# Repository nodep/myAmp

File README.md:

# modulo2

What started as an idea to upgrade the guts of a practice guitar amplifier (Marshall Valvestate 8010), has evolved into a stereo guitar amplifier with effects. The current prototype is housed in a guitar pedal box (119 x 93.5 x 56.5mm). It has a modular design with the preamp, the effects board, and a stereo power amp. These modules are split into their own PCBs.

### The preamp

It is based on ESP's project 27 (https://sound-au.com/project27.htm). I have only used the preamp from this project and I have made a few changes:

- The overdrive section is changed to work as protection and limit the output to 3.3V. This is needed for the inputs of the DSP chip in the effects section (max input of FV-1 is 3.3V).
- The zener diode rail splitter is changed to a TL2426. Reasons being a smaller footprint and much lower power consumption.
- The total gain has been reduced on every stage.
- The tone control values have changed to a more Fender-like sound.

### The effects

The effects sections is based on a Spin semiconductor's FV-1 DSP chip. The chip has 8 built-in effects and the ability to read 8 more effects from an external EEPROM. This was extended using a microcontroller (ATmega328p) to up to 50 external effects which are read from the microcontroller's flash memory. The board also has a dry/wet mixer, a master volume. The microcontroller has a driverless USB bootloader which allows easier firmware updates and DSP program modification. A rotary encoder allows for FV-1 program selection and changing the input clock frequency of the FV-1. Some of the FV-1 programs work as a mono input and produce a stereo output with one channel outputing a slightly different signal to the other creating a stereo effect from a mono preamp input. The microcontroller oversees the power section to avoid audible pops during the power-up and power-down.

### The power amp

The power section is based on a TPA3220 in a stereo configuration. I have not tested it fully yet, but it should be able to output up to 60W into 4Ω per channel. It is a Class-D amp bringing high efficiency (around 90%) and very low distortion and noise. The TPA3220 chip has an integrated preamp with a selectable gain (4 distinct levels) making the full range of the master volume useful for quiter practice and louder performance levels.

The PCBs for the final prototype have been send to the fab.

Stay tuned for results!

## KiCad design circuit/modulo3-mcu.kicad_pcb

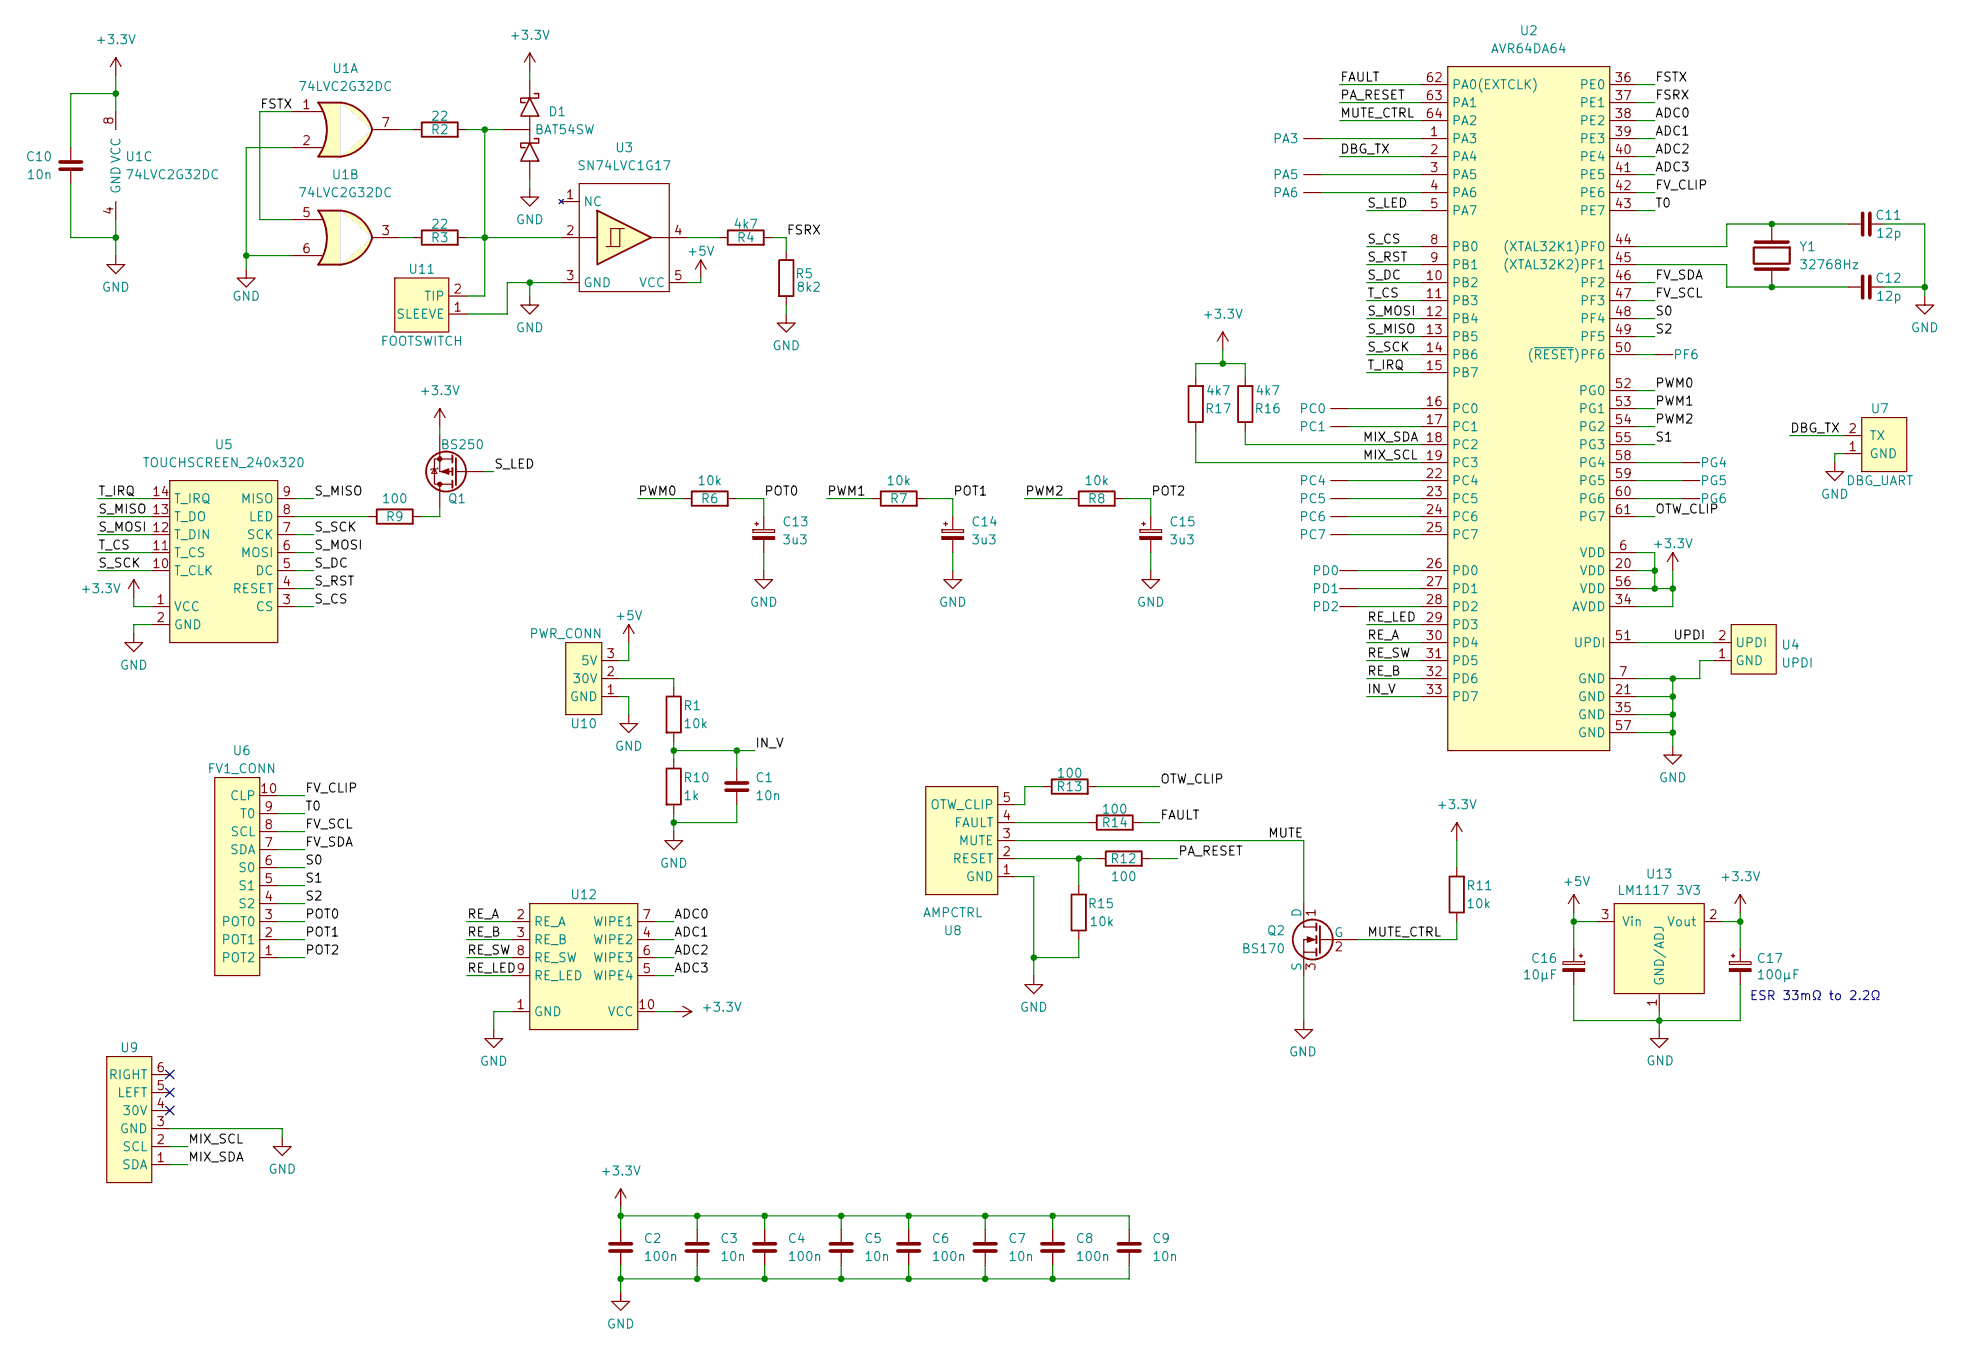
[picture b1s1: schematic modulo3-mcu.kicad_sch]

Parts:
C1, C3, C5, C7, C9, C10: 10n; C_1206
C2, C4, C6, C8: 100n; C_1206
C11, C12: 12p; C_1206
C13, C14, C15: 3u3; CPOL_D4_P1.5
C16: 10µF; CPOL_D4_P1.5
C17: 100µF; CPOL_D6.3_P2.5
D1: BAT54SW; SOT-23
Q1: BS250; TO-92_Inline_Wide
Q2: BS170; TO-92_Inline_Wide
R1, R6, R7, R8, R11, R15: 10k; R_10MM
R2, R3: 22; R_10MM
R4, R16, R17: 4k7; R_10MM
R5: 8k2; R_10MM
R9, R12, R13, R14: 100; R_10MM
R10: 1k; R_10MM
T1: PA3; TestPad
T2: PD2; TestPad
T3: PA6; TestPad
T4: PC0; TestPad
T5: PC1; TestPad
T6: PG5; TestPad
T7: PG4; TestPad
T8: PF6; TestPad
T9: PA5; TestPad
T10: PD1; TestPad
T11: PD0; TestPad
T12: PC7; TestPad
T13: PG6; TestPad
T14: PC4; TestPad
T15: PC5; TestPad
T16: PC6; TestPad
U1: 74LVC2G32DC; VSSOP-8_2.4x2.1mm_P0.5mm
U2: AVR64DA64; TQFP-64_10x10mm_P0.5mm
U3: SN74LVC1G17; SOT-23-5
U4: UPDI; UDPI
U5: TOUCHSCREEN_240x320; TOUCHSCREEN_2.8
U6: FV1_CONN
U7: DBG_UART
U8: AMPCTRL
U9: PREAMP_CONN
U10: PWR_CONN
U11: FOOTSWITCH; EXT_JACK
U12: KNOBS
U13: LM1117 3V3; SOT-223
Y1: 32768Hz; QUARTZ_85SMX

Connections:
+3.3V: C2.1, C3.1, C4.1, C5.1, C6.1, C7.1, C8.1, C9.1, C10.1, C17.1, D1.2, Q1.3 (S), R11.2, R16.2, R17.2, U1.8 (VCC), U2.6 (VDD), U2.20 (VDD), U2.34 (AVDD), U2.56 (VDD), U5.1 (VCC), U12.10 (VCC), U13.2 (Vout)
+5V: C16.1, U3.5 (VCC), U10.3 (5V), U13.3 (Vin)
/ADC0: U2.38 (PE2), U12.7 (WIPE1)
/ADC1: U2.39 (PE3), U12.4 (WIPE2)
/ADC2: U2.40 (PE4), U12.6 (WIPE3)
/ADC3: U2.41 (PE5), U12.5 (WIPE4)
/DBG_TX: U2.2 (PA4), U7.2 (TX)
/FAULT: R14.2, U2.62 (PA0(EXTCLK))
/FSRX: R4.2, R5.1, U2.37 (PE1)
/FSTX: U1.1, U1.5, U2.36 (PE0)
/FV_CLIP: U2.42 (PE6), U6.10 (CLP)
/FV_SCL: U2.47 (PF3), U6.8 (SCL)
/FV_SDA: U2.46 (PF2), U6.7 (SDA)
/IN_V: C1.1, R1.2, R10.1, U2.33 (PD7)
/MIX_SCL: R17.1, U2.19 (PC3), U9.2 (SCL)
/MIX_SDA: R16.1, U2.18 (PC2), U9.1 (SDA)
/MUTE: Q2.1 (D), U8.3 (MUTE)
/MUTE_CTRL: Q2.2 (G), R11.1, U2.64 (PA2)
/OTW_CLIP: R13.2, U2.61 (PG7)
/PA_RESET: R12.2, U2.63 (PA1)
/POT0: C13.1, R6.2, U6.3 (POT0)
/POT1: C14.1, R7.2, U6.2 (POT1)
/POT2: C15.1, R8.2, U6.1 (POT2)
/PWM0: R6.1, U2.52 (PG0)
/PWM1: R7.1, U2.53 (PG1)
/PWM2: R8.1, U2.54 (PG2)
/RE_A: U2.30 (PD4), U12.2 (RE_A)
/RE_B: U2.32 (PD6), U12.3 (RE_B)
/RE_LED: U2.29 (PD3), U12.9 (RE_LED)
/RE_SW: U2.31 (PD5), U12.8 (RE_SW)
/S0: U2.48 (PF4), U6.6 (S0)
/S1: U2.55 (PG3), U6.5 (S1)
/S2: U2.49 (PF5), U6.4 (S2)
/S_CS: U2.8 (PB0), U5.3 (CS)
/S_DC: U2.10 (PB2), U5.5 (DC)
/S_LED: Q1.2 (G), U2.5 (PA7)
/S_MISO: U2.13 (PB5), U5.9 (MISO), U5.13 (T_DO)
/S_MOSI: U2.12 (PB4), U5.6 (MOSI), U5.12 (T_DIN)
/S_RST: U2.9 (PB1), U5.4 (RESET)
/S_SCK: U2.14 (PB6), U5.7 (SCK), U5.10 (T_CLK)
/T0: U2.43 (PE7), U6.9 (T0)
/T_CS: U2.11 (PB3), U5.11 (T_CS)
/T_IRQ: U2.15 (PB7), U5.14 (T_IRQ)
/UPDI: U2.51 (UPDI), U4.2 (UPDI)
GND: C1.2, C2.2, C3.2, C4.2, C5.2, C6.2, C7.2, C8.2, C9.2, C10.2, C11.2, C12.2, C13.2, C14.2, C15.2, C16.2, C17.2, D1.1, Q2.3 (S), R5.2, R10.2, R15.1, U1.2, U1.4 (GND), U1.6, U2.7 (GND), U2.21 (GND), U2.35 (GND), U2.57 (GND), U3.3 (GND), U4.1 (GND), U5.2 (GND), U7.1 (GND), U8.1 (GND), U9.3 (GND), U10.1 (GND), U11.1 (SLEEVE), U12.1 (GND), U13.1 (GND/ADJ)
unnamed: Q1.1 (D), R9.2
unnamed: R2.1, U1.7
unnamed: R3.1, U1.3
unnamed: R4.1, U3.4
unnamed: C11.1, U2.44 ((XTAL32K1)PF0), Y1.1
unnamed: C12.1, U2.45 ((XTAL32K2)PF1), Y1.2
unnamed: T8.1, U2.50 ((~RESET)PF6)
unnamed: T1.1, U2.1 (PA3)
unnamed: T9.1, U2.3 (PA5)
unnamed: T3.1, U2.4 (PA6)
unnamed: T4.1, U2.16 (PC0)
unnamed: T5.1, U2.17 (PC1)
unnamed: T14.1, U2.22 (PC4)
unnamed: T15.1, U2.23 (PC5)
unnamed: T16.1, U2.24 (PC6)
unnamed: T12.1, U2.25 (PC7)
unnamed: T11.1, U2.26 (PD0)
unnamed: T10.1, U2.27 (PD1)
unnamed: T2.1, U2.28 (PD2)
unnamed: T7.1, U2.58 (PG4)
unnamed: T6.1, U2.59 (PG5)
unnamed: T13.1, U2.60 (PG6)
unnamed: R9.1, U5.8 (LED)
unnamed: R14.1, U8.4 (FAULT)
unnamed: R13.1, U8.5 (OTW_CLIP)
unnamed: R12.1, R15.2, U8.2 (RESET)
unnamed: R1.1, U10.2 (30V)
unnamed: D1.3, R2.2, R3.2, U3.2, U11.2 (TIP)

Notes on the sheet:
ESR 33mΩ to 2.2Ω

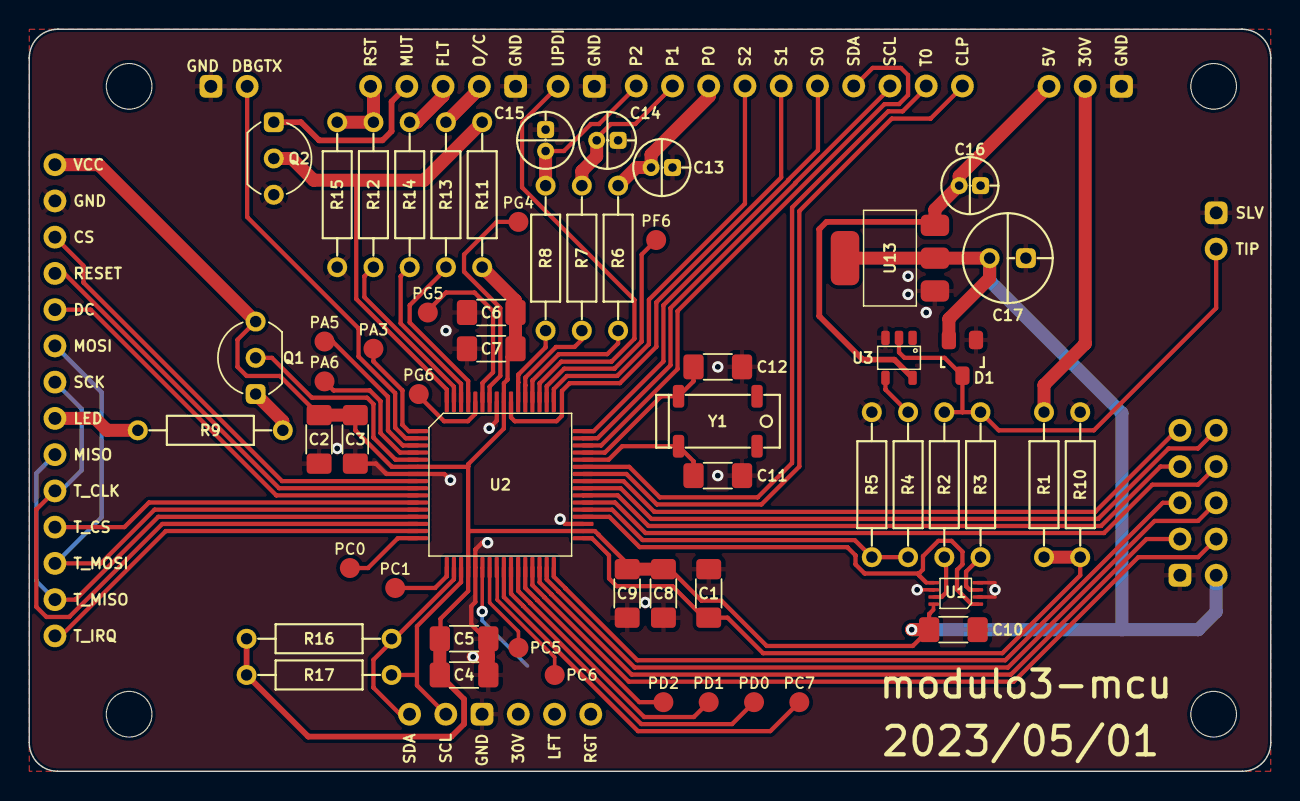
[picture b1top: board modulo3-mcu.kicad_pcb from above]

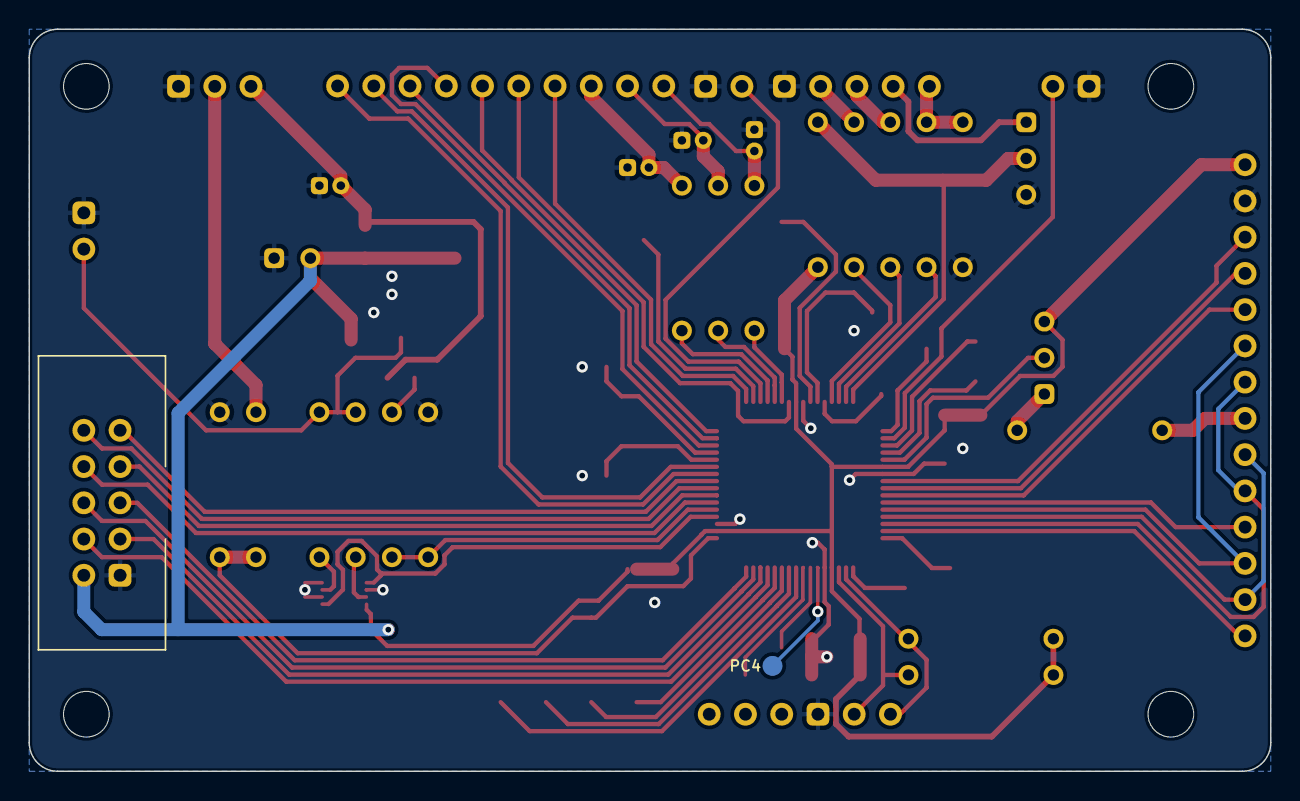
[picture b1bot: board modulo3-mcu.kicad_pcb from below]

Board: 2 copper layers, 87.0 x 52.0 mm, 67 parts (2 on the bottom side), 73 nets.

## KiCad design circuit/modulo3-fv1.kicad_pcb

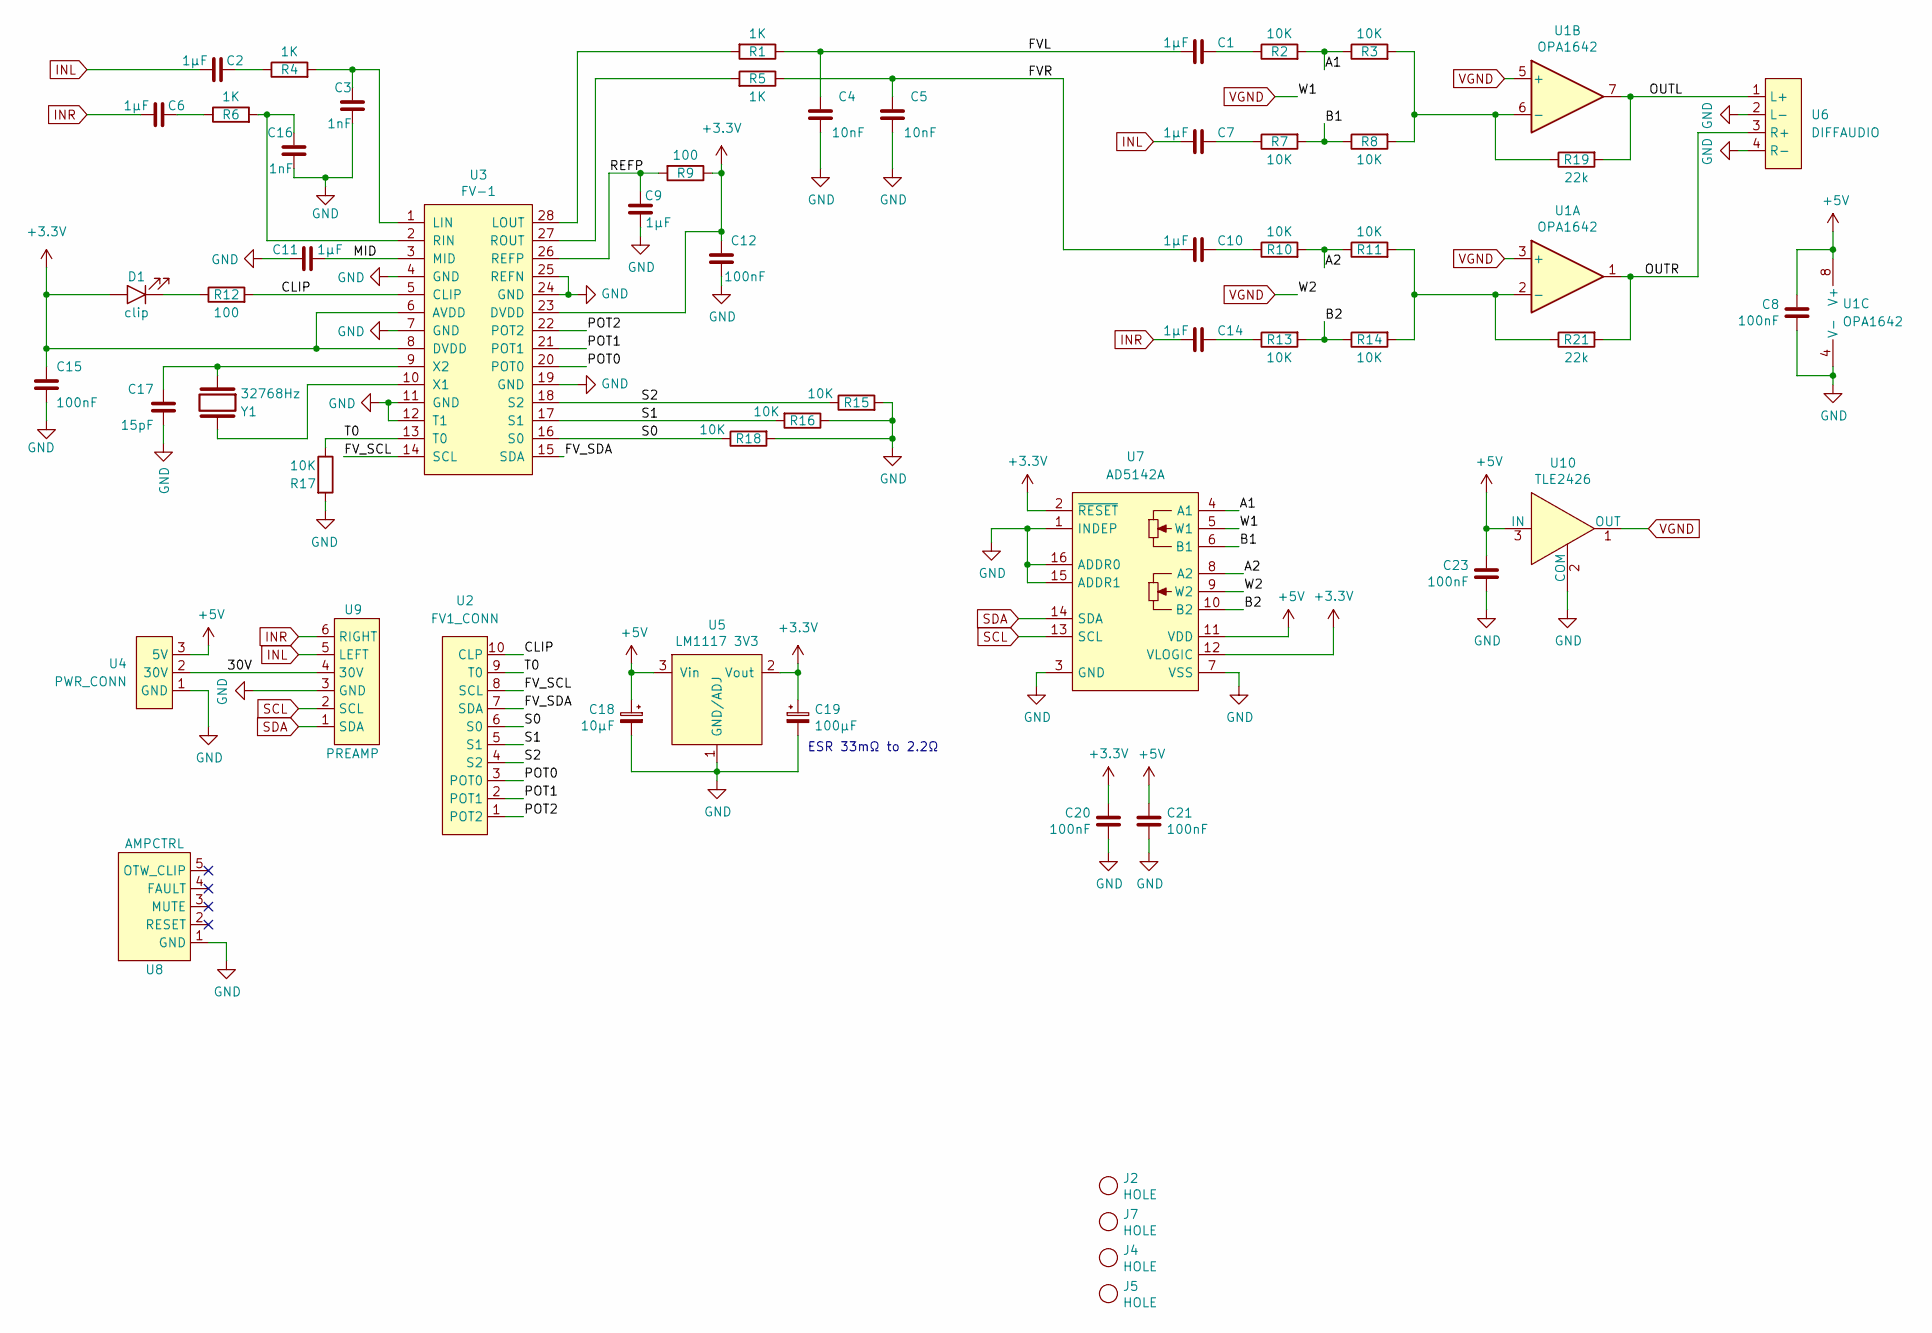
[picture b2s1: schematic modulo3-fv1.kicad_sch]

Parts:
C1, C2, C6, C7, C10, C14: 1µF; C_FILM_L7.2mm_W5.0mm_P5.00mm
C3, C16: 1nF; C_1206
C4, C5: 10nF; C_1206
C8, C12, C15, C20, C21, C23: 100nF; C_1206
C9, C11: 1µF; C_1206
C17: 15pF; C_1206
C18: 10µF; CPOL_D4_P1.5
C19: 100µF; CPOL_D6.3_P2.5
D1: clip; LED_D3.0mm
J2, J4, J5, J7: HOLE; MountingHole
R1, R4, R5, R6: 1K; R_10MM
R2, R3, R7, R8, R10, R11, R13, R14, R15, R16, R17, R18: 10K; R_10MM
R9, R12: 100; R_10MM
R19, R21: 22k; R_10MM
U1: OPA1642; SOIC-8_3.9x4.9mm_P1.27mm
U2: FV1_CONN
U3: FV-1; SOIC-28_7.5x17.9mm_Pitch1.27mm
U4: PWR_CONN
U5: LM1117 3V3; SOT-223
U6: DIFFAUDIO
U7: AD5142A; TSSOP-16_4.4x5mm_P0.65mm
U8: AMPCTRL
U9: PREAMP; PREAMP_CONN
U10: TLE2426; TO-92_Inline_Wide
Y1: 32768Hz; QUARTZ_85SMX

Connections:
+3V3: C12.1, C15.2, C19.1, C20.2, D1.2 (A), R9.1, U3.6 (AVDD), U3.8 (DVDD), U3.23 (DVDD), U5.2 (Vout), U7.2 (~RESET), U7.12 (VLOGIC)
+5V: C8.2, C18.1, C21.2, C23.2, U1.8 (V+), U4.3 (5V), U5.3 (Vin), U7.11 (VDD), U10.3 (IN)
/30V: U4.2 (30V), U9.4 (30V)
/A1: R2.2, R3.1, U7.4 (A1)
/A2: R10.2, R11.1, U7.8 (A2)
/B1: R7.2, R8.1, U7.6 (B1)
/B2: R13.2, R14.1, U7.10 (B2)
/CLIP: R12.2, U2.10 (CLP), U3.5 (CLIP)
/FVL: C1.1, C4.1, R1.1
/FVR: C5.1, C10.1, R5.1
/FV_SCL: U2.8 (SCL), U3.14 (SCL)
/FV_SDA: U2.7 (SDA), U3.15 (SDA)
/MID: C11.2, U3.3 (MID)
/OUTL: R19.2, U1.7, U6.1 (L+)
/OUTR: R21.2, U1.1, U6.3 (R+)
/POT0: U2.3 (POT0), U3.20 (POT0)
/POT1: U2.2 (POT1), U3.21 (POT1)
/POT2: U2.1 (POT2), U3.22 (POT2)
/REFP: C9.1, R9.2, U3.26 (REFP)
/S0: R18.1, U2.6 (S0), U3.16 (S0)
/S1: R16.2, U2.5 (S1), U3.17 (S1)
/S2: R15.1, U2.4 (S2), U3.18 (S2)
/T0: R17.1, U2.9 (T0), U3.13 (T0)
GND: C3.1, C4.2, C5.2, C8.1, C9.2, C11.1, C12.2, C15.1, C16.1, C17.1, C18.2, C19.2, C20.1, C21.1, C23.1, R15.2, R16.1, R17.2, R18.2, U1.4 (V-), U3.4 (GND), U3.7 (GND), U3.11 (GND), U3.12 (T1), U3.19 (GND), U3.24 (GND), U3.25 (REFN), U4.1 (GND), U5.1 (GND/ADJ), U6.2 (L-), U6.4 (R-), U7.1 (INDEP), U7.3 (GND), U7.7 (VSS), U7.15 (ADDR1), U7.16 (ADDR0), U8.1 (GND), U9.3 (GND), U10.2 (COM)
INL: C2.2, C7.1, U9.5 (LEFT)
INR: C6.2, C14.1, U9.6 (RIGHT)
unnamed: C1.2, R2.1
unnamed: C2.1, R4.1
unnamed: C6.1, R6.1
unnamed: C7.2, R7.1
unnamed: C10.2, R10.1
unnamed: C14.2, R13.1
unnamed: D1.1 (K), R12.1
unnamed: R11.2, R14.2, R21.1, U1.2 (-)
unnamed: R3.2, R8.2, R19.1, U1.6 (-)
unnamed: C3.2, R4.2, U3.1 (LIN)
unnamed: R1.2, U3.28 (LOUT)
unnamed: C16.2, R6.2, U3.2 (RIN)
unnamed: R5.2, U3.27 (ROUT)
unnamed: U3.10 (X1), Y1.2
unnamed: C17.2, U3.9 (X2), Y1.1
SCL: U7.13 (SCL), U9.2 (SCL)
SDA: U7.14 (SDA), U9.1 (SDA)
VGND: U1.3 (+), U1.5 (+), U7.5 (W1), U7.9 (W2), U10.1 (OUT)

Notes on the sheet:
ESR 33mΩ to 2.2Ω

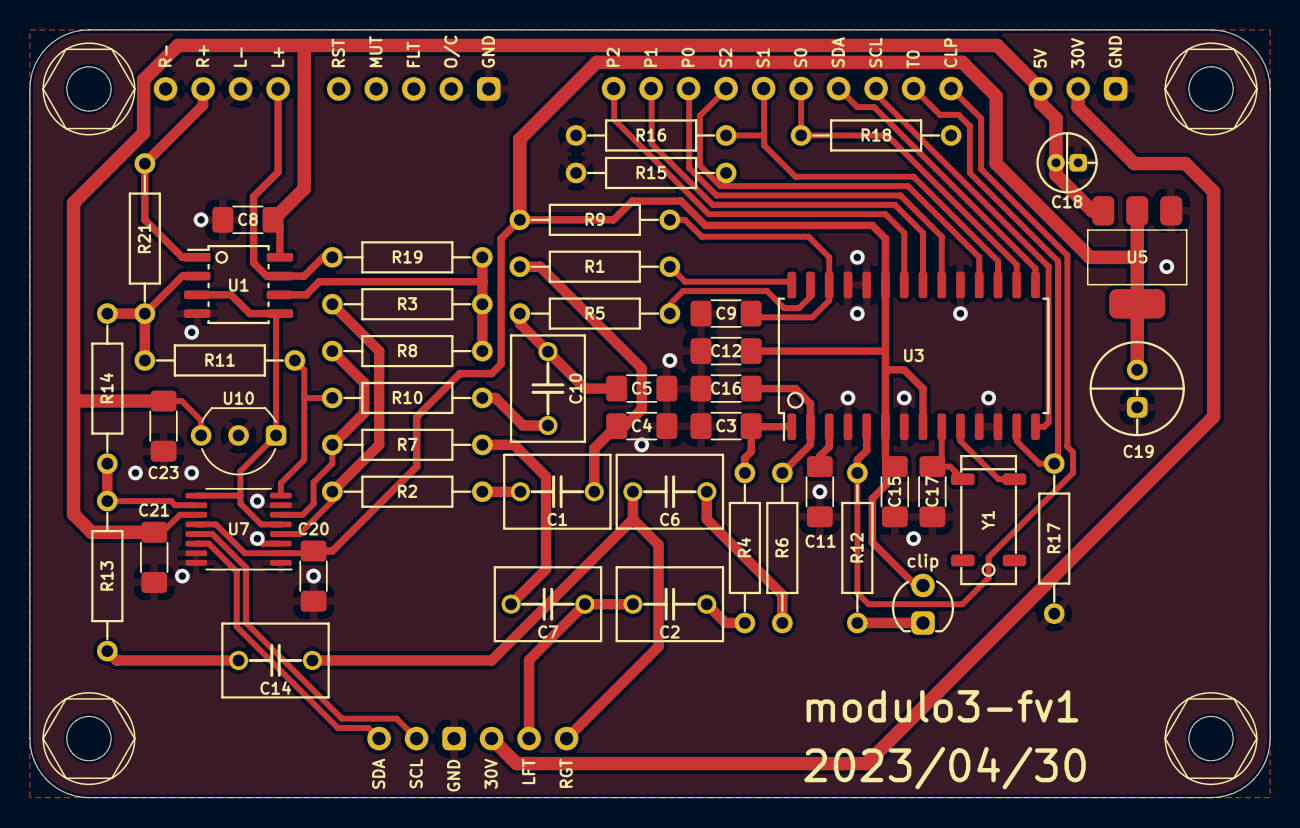
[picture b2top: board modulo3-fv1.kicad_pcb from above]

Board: 2 copper layers, 84.0 x 52.0 mm, 57 parts (0 on the bottom side), 44 nets.

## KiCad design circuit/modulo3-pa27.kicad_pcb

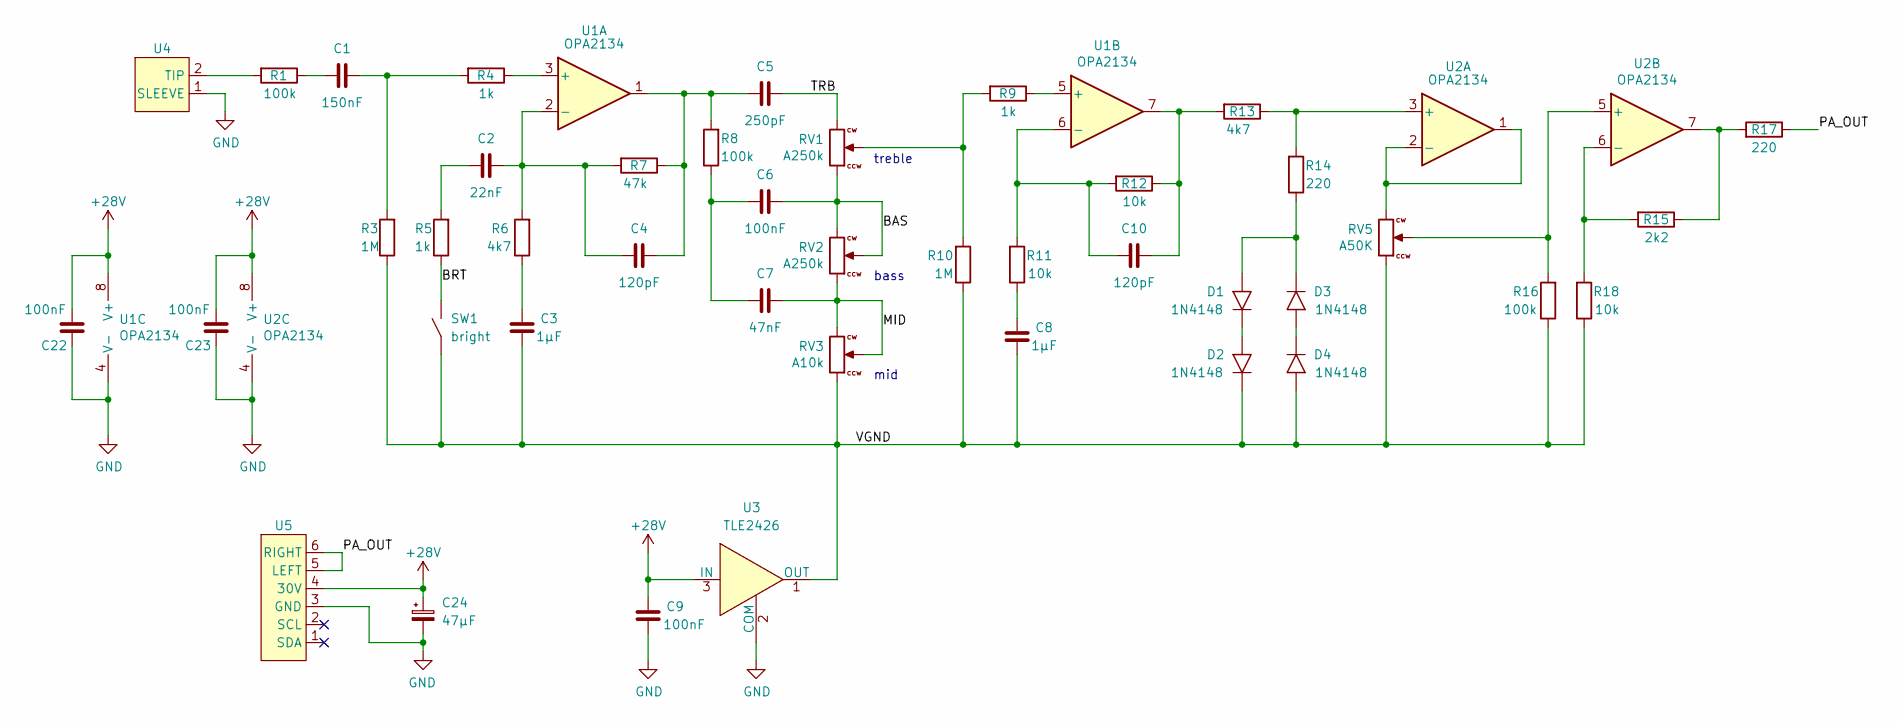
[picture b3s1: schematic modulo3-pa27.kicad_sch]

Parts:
C1: 150nF; C_FILM_L7.2mm_W3.5mm_P5.00mm
C2: 22nF; C_FILM_L7.2mm_W3.5mm_P5.00mm
C3, C8: 1µF; C_FILM_L7.2mm_W5.0mm_P5.00mm
C4, C10: 120pF; C_2.5MM
C5: 250pF; C_2.5MM
C6: 100nF; C_FILM_L7.2mm_W3.5mm_P5.00mm
C7: 47nF; C_FILM_L7.2mm_W3.5mm_P5.00mm
C9, C22, C23: 100nF; C_1206
C24: 47µF; CPOL_D6.3_P2.5
D1, D2, D3, D4: 1N4148; DO35
R1, R8, R16: 100k; R_10MM
R3, R10: 1M; R_10MM
R4, R5, R9: 1k; R_10MM
R6, R13: 4k7; R_10MM
R7: 47k; R_10MM
R11, R12, R18: 10k; R_10MM
R14, R17: 220; R_10MM
R15: 2k2; R_10MM
RV1, RV2: A250k; BOURNS_PTD901_xx15K
RV3: A10k; BOURNS_PTD901_xx15K
RV5: A50K; BOURNS_PTD901_xx15K
SW1: bright; JUMPER
U1, U2: OPA2134; DIP-8
U3: TLE2426; TO-92_Inline_Wide
U4: EXT_JACK
U5: PREAMP_CONN

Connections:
+28V: C9.2, C22.2, C23.2, C24.1, U1.8 (V+), U2.8 (V+), U3.3 (IN), U5.4 (30V)
/BAS: C6.2, RV1.1, RV2.2, RV2.3
/BRT: R5.1, SW1.2
/MID: C7.2, RV2.1, RV3.2, RV3.3
/PA_OUT: R17.1, U5.5 (LEFT), U5.6 (RIGHT)
/TRB: C5.2, RV1.3
/VGND: C3.1, C8.1, D2.1 (K), D4.2 (A), R3.1, R10.1, R16.1, R18.1, RV3.1, RV5.1, SW1.1, U3.1 (OUT)
GND: C9.1, C22.1, C23.1, C24.2, U1.4 (V-), U2.4 (V-), U3.2 (COM), U4.1 (SLEEVE), U5.3 (GND)
unnamed: C1.1, R1.1
unnamed: C1.2, R3.2, R4.2
unnamed: C2.1, R5.2
unnamed: C3.2, R6.1
unnamed: C4.2, C5.1, R7.1, R8.2, U1.1
unnamed: C6.1, C7.1, R8.1
unnamed: C8.2, R11.1
unnamed: C10.2, R12.1, R13.2, U1.7
unnamed: D1.2 (A), D3.1 (K), R14.1
unnamed: D1.1 (K), D2.2 (A)
unnamed: D3.2 (A), D4.1 (K)
unnamed: R9.2, R10.2, RV1.2
unnamed: R15.1, R17.2, U2.7
unnamed: R4.1, U1.3 (+)
unnamed: C2.2, C4.1, R6.2, R7.2, U1.2 (-)
unnamed: R9.1, U1.5 (+)
unnamed: C10.1, R11.2, R12.2, U1.6 (-)
unnamed: R13.1, R14.2, U2.3 (+)
unnamed: RV5.3, U2.1, U2.2 (-)
unnamed: R16.2, RV5.2, U2.5 (+)
unnamed: R15.2, R18.2, U2.6 (-)
unnamed: R1.2, U4.2 (TIP)

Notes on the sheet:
treble
bass
mid

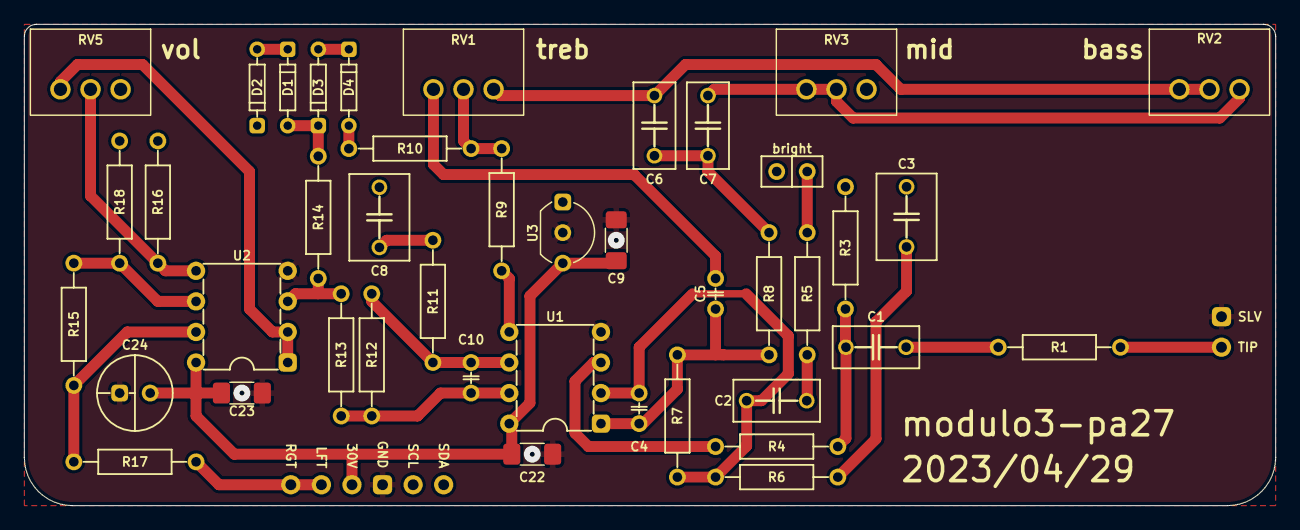
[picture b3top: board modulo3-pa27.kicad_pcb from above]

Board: 2 copper layers, 104.0 x 40.0 mm, 44 parts (0 on the bottom side), 30 nets.

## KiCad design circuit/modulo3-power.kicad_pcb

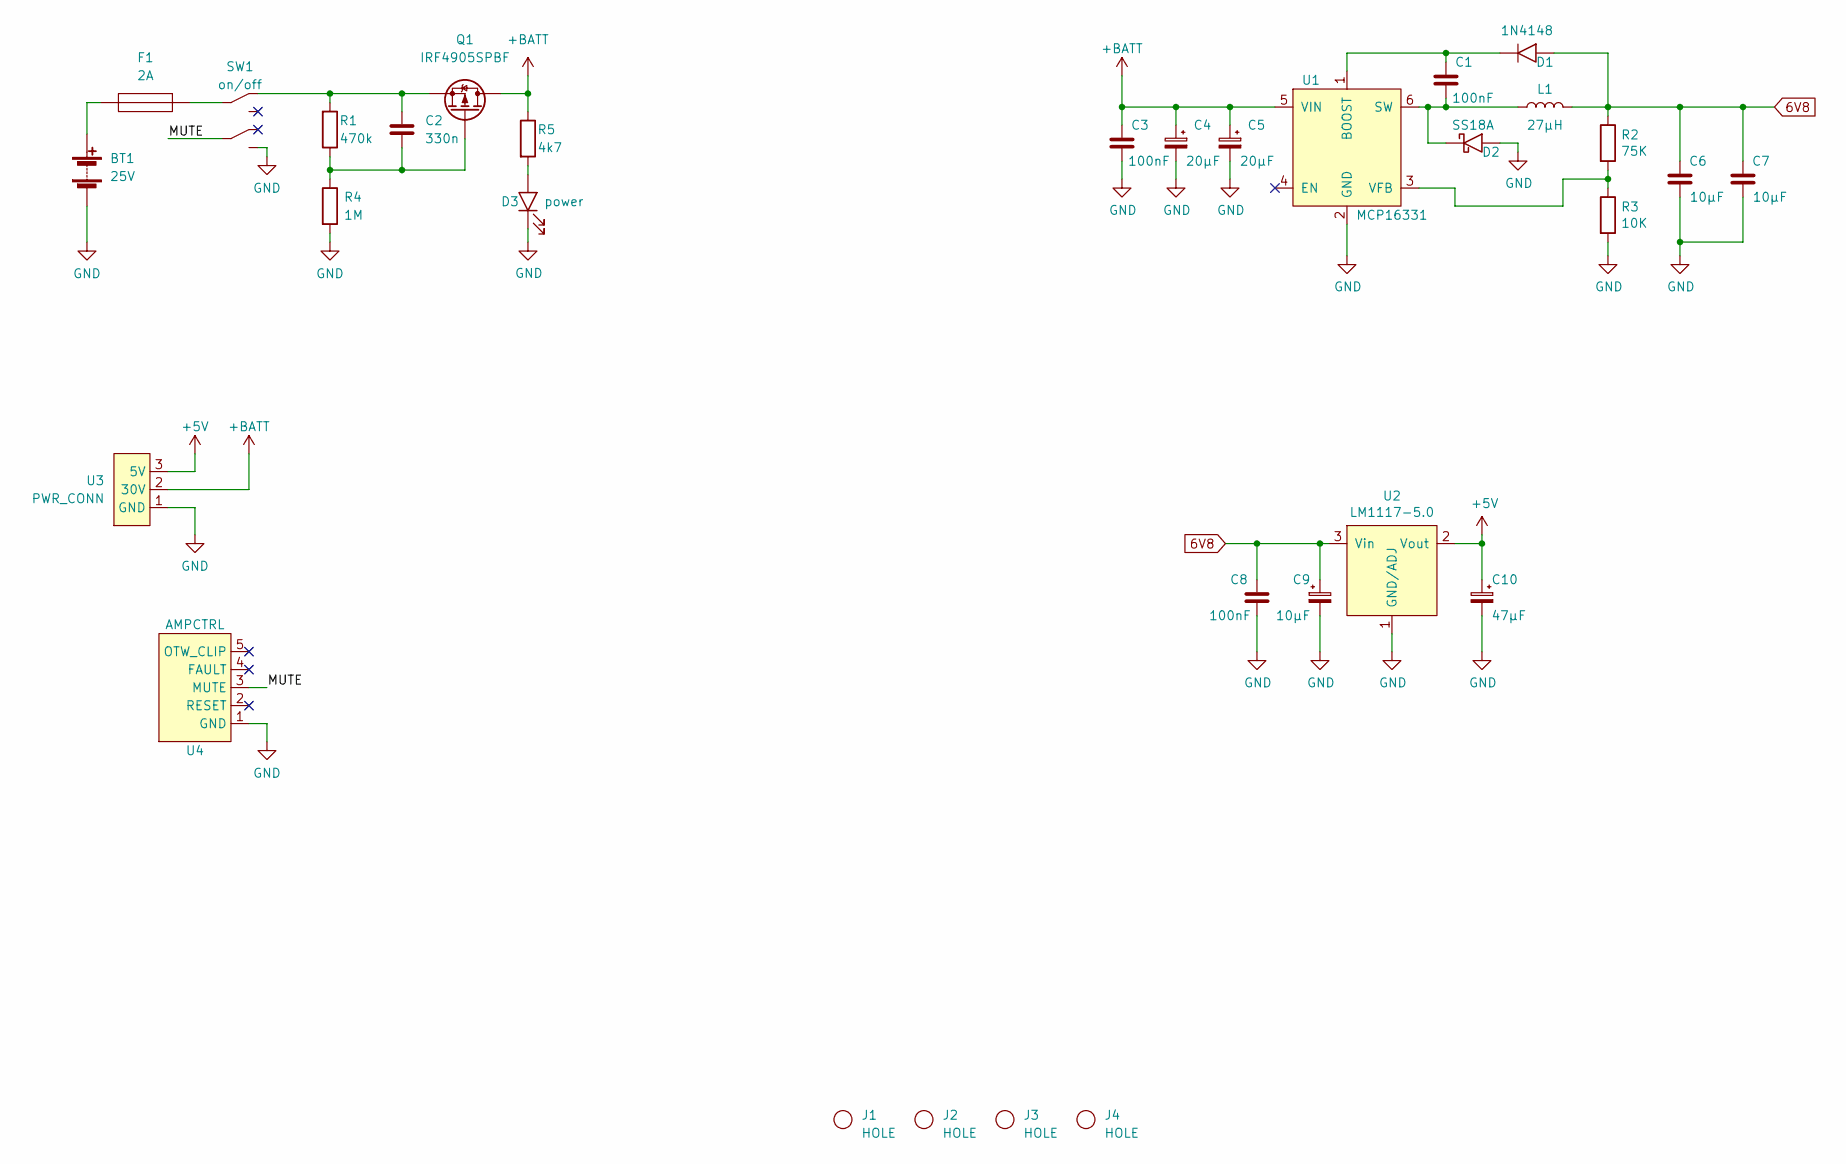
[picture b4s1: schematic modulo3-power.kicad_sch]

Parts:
BT1: 25V; XT60-M
C1, C3, C8: 100nF; C_1206
C2: 330n; C_5.0MM
C4, C5: 20μF; CPOL_D6.3_P2.5
C6, C7: 10μF; C_1812
C9: 10μF; CPOL_D4_P1.5
C10: 47μF; CPOL_D4_P1.5
D1: 1N4148; DO35
D2: SS18A; D_SMA
D3: power; LED_D3.0mm
F1: 2A; MF-LSMF
J1, J2, J3, J4: HOLE; MountingHole
L1: 27μH; COIL_DER0705
Q1: IRF4905SPBF; D2PAK
R1: 470k; R_10MM
R2: 75K; R_0805
R3: 10K; R_0805
R4: 1M; R_10MM
R5: 4k7; R_10MM
SW1: on/off; SW_DPDT
U1: MCP16331; SOT-23-6
U2: LM1117-5.0; TO-252-3
U3: PWR_CONN
U4: AMPCTRL

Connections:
6V8: C6.2, C7.2, C8.2, C9.1, D1.2 (A), L1.2, R2.1, U2.3 (Vin)
+5V: C10.1, U2.2 (Vout), U3.3 (5V)
+BATT: C3.2, C4.1, C5.1, Q1.2 (D), R5.1, U1.5 (VIN), U3.2 (30V)
/MUTE: SW1.5, U4.3 (MUTE)
GND: BT1.2 (-), C3.1, C4.2, C5.2, C6.1, C7.1, C8.1, C9.2, C10.2, D2.2 (A), D3.1 (K), R3.2, R4.2, SW1.6, U1.2 (GND), U2.1 (GND/ADJ), U3.1 (GND), U4.1 (GND)
unnamed: BT1.1 (+), F1.1
unnamed: C1.2, D1.1 (K), U1.1 (BOOST)
unnamed: C1.1, D2.1 (K), L1.1, U1.6 (SW)
unnamed: D3.2 (A), R5.2
unnamed: F1.2, SW1.2
unnamed: C2.2, Q1.1 (G), R1.1, R4.1
unnamed: C2.1, Q1.3 (S), R1.2, SW1.1
unnamed: R2.2, R3.1, U1.3 (VFB)

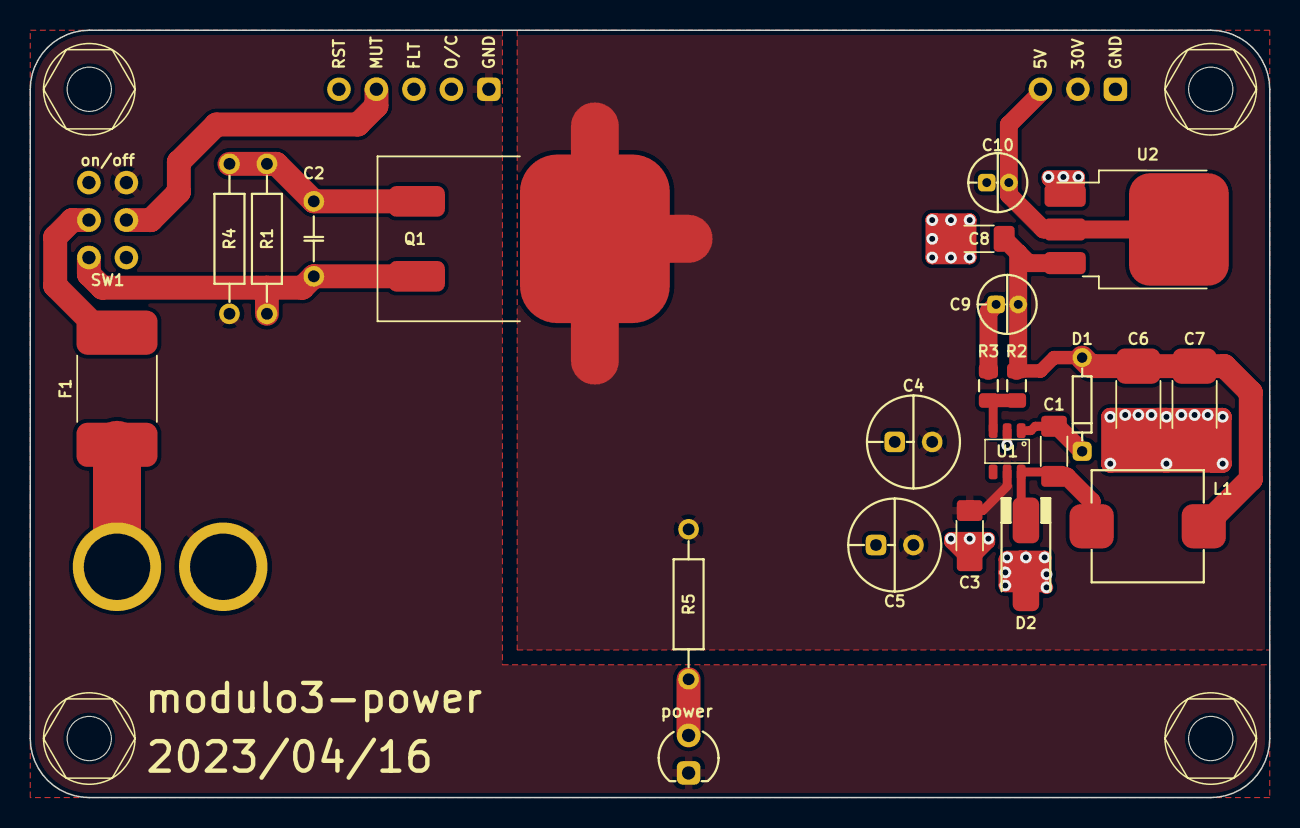
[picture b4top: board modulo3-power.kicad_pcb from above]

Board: 2 copper layers, 84.0 x 52.0 mm, 31 parts (1 on the bottom side), 13 nets.

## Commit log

2020-02-17 inital commit
2020-02-17 added fender tone stack
2020-02-18 added CRL footprints and gitignore
2020-02-18 added power amp to schematic; added more footprints
2020-02-18 changed resistor value
2020-02-18 schematic done; PCB started
2020-02-19 small changes
2020-02-19 very rough layout
2020-02-23 more layout
2020-02-27 some 3D model references corrected
2020-02-27 trace widths
2020-02-27 started routing
2020-02-28 routing mostly done
2020-04-29 modular version in beta
2020-05-03 sent to fab
2020-05-14 this one was actually sent
2020-05-21 started routing FV-1 breakout
2020-05-25 came up with the name: RedMyst
2020-05-27 RedMyst continued
2020-05-29 RedMyst continued...
2020-05-30 added alps 3d models
2020-05-30 labels
2020-05-31 localiced 3d models
2020-05-31 moved step files to models
2020-06-01 layout done; starting routing
2020-06-02 routing continued...
2020-06-03 routing done
2020-06-03 final touches
2020-06-04 and continued...
2020-06-07 red myst (which is green) is routed... and abandoned
2020-06-08 scrapped RedMyst; started modulo
2020-06-09 started routing the preamp
2020-06-09 preamp layout started
2020-06-10 fully modularized!
2020-06-10 half way laying out the mixer
2020-06-11 added render
2020-06-11 even more layout
2020-06-11 small updates
2020-06-12 added DC-DC converter
2020-06-14 small changes on pcb
2020-06-15 added WR
2020-06-16 placed the bus
2020-06-16 routing power & mcu
2020-06-17 routed power amp
2020-06-17 10k audio pot in the mixer
2020-06-18 routed FV-1 and the mixer
2020-06-18 first routing done
2020-06-18 added pot and rotenc datasheets; cosmetics
2020-06-19 ccw/cw on pots; new values of the tone stack
2020-06-19 front copper plant; pot descriptions
2020-06-21 this one goes to fab
2020-06-23 fresh render; cosmetic changes in the mcu & power schematic
2020-06-23 downscaled the render image
2020-07-27 AVR software started; small hardware problems fixed
2020-07-29 this seems to be working :)
2020-07-29 fixed constant in refresh_program
2020-07-30 this is working with 7 banks
2021-11-21 Sent modulo2 power amp to PCB fab
2021-11-30 before rev 2 of the power amp
2021-12-10 Added master volume
2021-12-16 master volume with TMB tone stack; fv1 initial
2021-12-19 cleanup the the power amp a bit; still need to move the diff inputs
2022-01-02 master done (hopefully...)
2022-01-03 master moved to kicad 6 (yikes!)
2022-01-03 moved last 3d models to project
2022-01-07 added new preamp sim
2022-01-09 added pa27
2022-01-11 further routing
2022-01-11 redone layout and tracing
2022-01-15 made a toner transfer pa27
2022-01-31 made FV-1 prototype; converted kicad 5 files to kicad 6
2022-02-04 FV-1 firmware reworked for the new board; FV-1 PCB needs rework to correct errors
2022-02-06 rotenc switch and LEDs are working
2022-02-06 added report on createBanks.py; started PCB redesign
2022-02-07 routing powamp
2022-02-07 routed pa27; routing fv-1
2022-02-09 further routing of FV-1
2022-02-09 no more assembler; more routing
2022-02-10 no more program banks; programs are now independent
2022-02-13 small powamp changes
2022-02-15 getting closer to the final PCBs; still have to change the rotenc
2022-02-16 found new switch for gain select; eq needs redesign
2022-02-19 usb has been changed to accommodate fab capabilities; moved the rotenc deeper into the board
2022-02-19 routed eq pcb
2022-02-21 ditched the LED array board; LEDs are on the main PCB now
2022-02-22 tweaked program selector LEDs
2022-02-26 almost there...
2022-02-28 sent to fab!
2022-02-28 changed readme
2022-03-12 added D and RT to symbols
2022-03-16 added simple 3D render of PCBs for the enclosure
2022-03-20 fixed mistakes from assembly; added bootloader; firmware changed for PCB
2022-03-21 updated 3d model
2022-03-21 updated 3d model (again)
2022-03-23 power supervisor in alpha, still needs tweaking
2022-03-24 button events and debouncing
2022-03-25 bugfix in timer
2022-03-25 reduced preamp gain to not clip the FV-1; timer_ticks_high();
2022-03-26 LED flashing reworked
2022-03-27 battery voltage warning and display
2022-03-28 rotenc stabilize; fixed led_show() bug
2022-03-28 bugfixes in rotary encoder
2022-03-31 started new led speed
2022-03-31 led speed done
2022-04-03 comments and the box template
2022-04-15 power off brown-out removed
2022-04-15 added modulo3 box
2022-05-05 added inrush current sym; modulo3 box
2022-09-10 added PDFs for modulo2
2022-09-14 reworked the cabinet model
2022-09-20 asked for a quote on the cab(s)
2022-12-18 started modulo3; added FV-1 programs
2023-01-10 mcu board; fv1 board tracing
2023-01-13 added avr64da pinout table
2023-01-23 added touchscreen footprint
2023-01-28 typo in pinout XL
2023-01-29 general layout and board sizes
2023-02-11 added ampctrl and diffaudio; started changing powamp
2023-02-17 got the pcs and holes sizes for mcu, poweamp and fv1
2023-02-19 fv-1 mostly done; power progressed
2023-02-26 lotsa things :)
2023-03-12 futher...
2023-03-12 routing mcu
2023-03-15 mcu pcb first draft done!
2023-03-15 added test pads for unused mcu pins
2023-03-15 tweaked power amp and fv1
2023-03-19 ready to panelize
2023-03-19 panelized and sent to aisler
2023-04-16 attempt to send to fab: part II
2023-04-23 updated zone fill edge on pa27; moved modulo2 source
2023-04-25 fixed p mosfet for screen LED; started src
2023-04-27 added fonts and vscode
2023-04-29 fixed blunder in pa27; added stubs for some of the source files
2023-04-30 iopin added PORTG; fv1 progressed
2023-05-01 lowered the watch resolution to .24 ms; moved the pins of the display; added pull-ups for mix i2c
2023-05-02 starting proper architecture
2023-05-03 restructure rotenc
2023-05-05 rotenc working; tweaks on tick<->ms conversion
2023-05-05 added battery voltage ADC
2023-05-06 further
2023-05-14 first version of programs in flash
2023-05-14 strings are now in PROGMEM
2023-05-14 twaked json2cpp.py
2023-05-15 i2c slave working
2023-05-15 program send working, but very ugly
2023-05-20 send_program() is working and lean
2023-05-20 cleanup ADC and added noise gate
2023-05-21 reverted adc::is_new(); started eeprom
2023-05-31 added eeprom load/save but not tested yet
2023-05-31 preset load/save is working; need to set EESAVE to 1 to preserve the eeprom between flashes
2023-10-18 we have returned
2023-10-26 more fonts; voltage bar on display
2023-10-29 progress bars seem to be working; fixed bug in fill_rect
2023-10-29 wet/dry is not correctly printed; fixed coordinate bug in text print
2023-10-29 optimised progress bars
2023-10-29 more optimisation
2023-10-29 not showing unused params
2023-10-30 voltage bar optimized; fonts offset needs more tests
2023-11-01 added pedals drawings
2023-11-12 assembled and tested; power amp working; problem with noise from EXP pedal coupled into preamp/mix
2023-11-14 brown-out added; cleaned up some FV-1 programs
2023-11-15 small tweaks
2023-11-19 low battery from 3.2V to 3.5V
2023-11-19 cleaned up the list of included programs
2024-12-01 tweaks & debug
2024-12-01 fixes with preset loading
